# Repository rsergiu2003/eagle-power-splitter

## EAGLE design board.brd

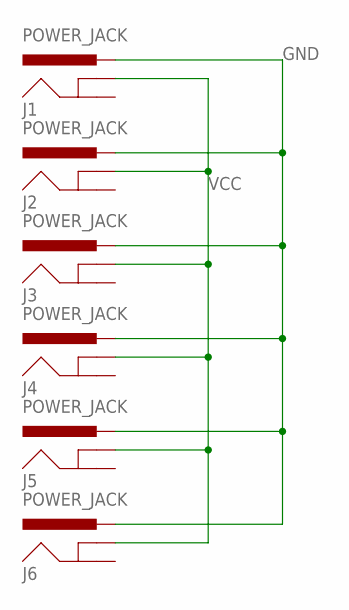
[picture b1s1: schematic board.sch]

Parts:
J1, J2, J3, J4, J5, J6: POWER_JACK; POWER_JACK_PTH

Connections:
GND: J1.PWR, J2.PWR, J3.PWR, J4.PWR, J5.PWR, J6.PWR
VCC: J1.GNDBREAK, J2.GNDBREAK, J3.GNDBREAK, J4.GNDBREAK, J5.GNDBREAK, J6.GNDBREAK

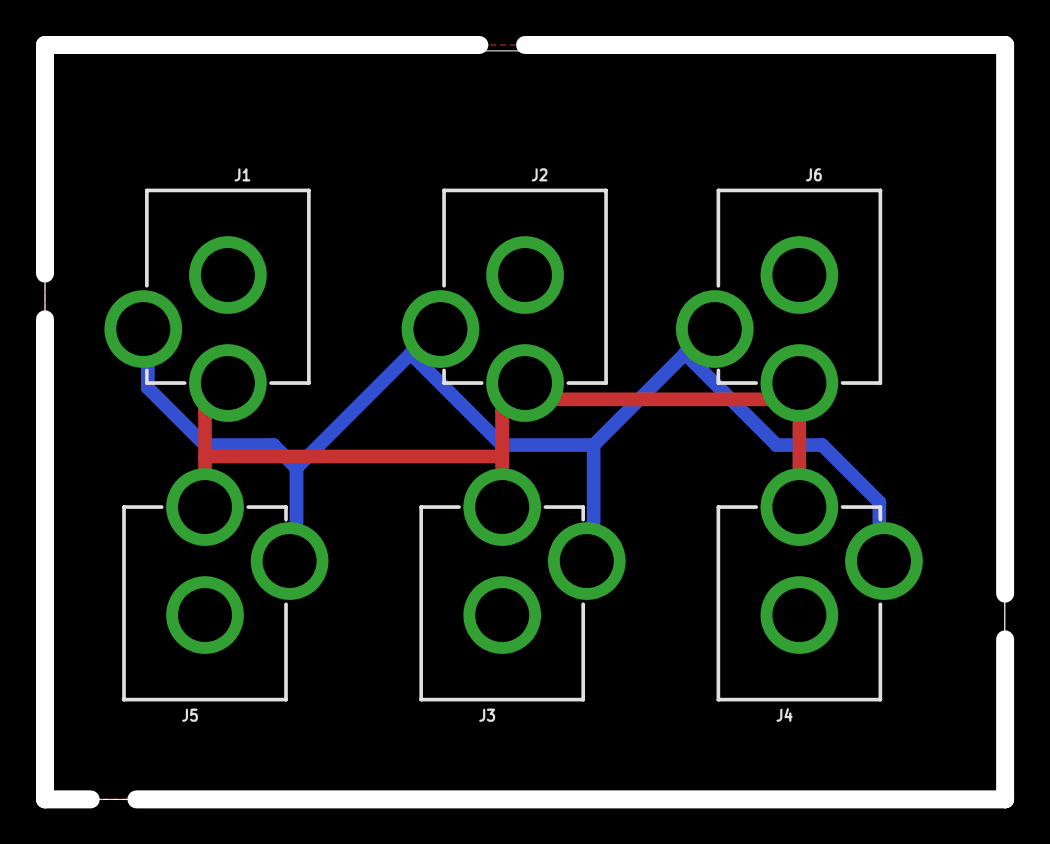
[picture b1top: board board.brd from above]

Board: 2 copper layers, 53.3 x 41.9 mm, 6 parts (0 on the bottom side), 2 nets.

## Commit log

2019-03-02 initial import
2019-03-02 images
2019-03-02 render image
2019-03-26 git ignore, add cooper fills (for testing)
